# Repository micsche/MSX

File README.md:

# MSX
Recreate a Z80 system using MSX2 standard. 

The system is subdivided into 5 boards connected by a BUS. 

1. msx1-cpu: This is the CPU board complete with CPU, Clock circuit, Reset Circuit, IO Address decoder and default MSX Wait circuit.
2. msx1-memory : This is the 64k ROM/ 64k RAM circuit and a USB Serial connection via CJMCU-232H. Currently this is an MSX1 standard. 
3. msx1-keyb-ppi : This is the Keyboard connector circuit and the Memory Slot selector circuit
4. msx1-psg: This is the sound circuit (using YM2149). Joystick interface not implemented.
5. msx1-vdp: This is the video circuit (using TMS9958). To be completed: VRAM  of 96k possible.

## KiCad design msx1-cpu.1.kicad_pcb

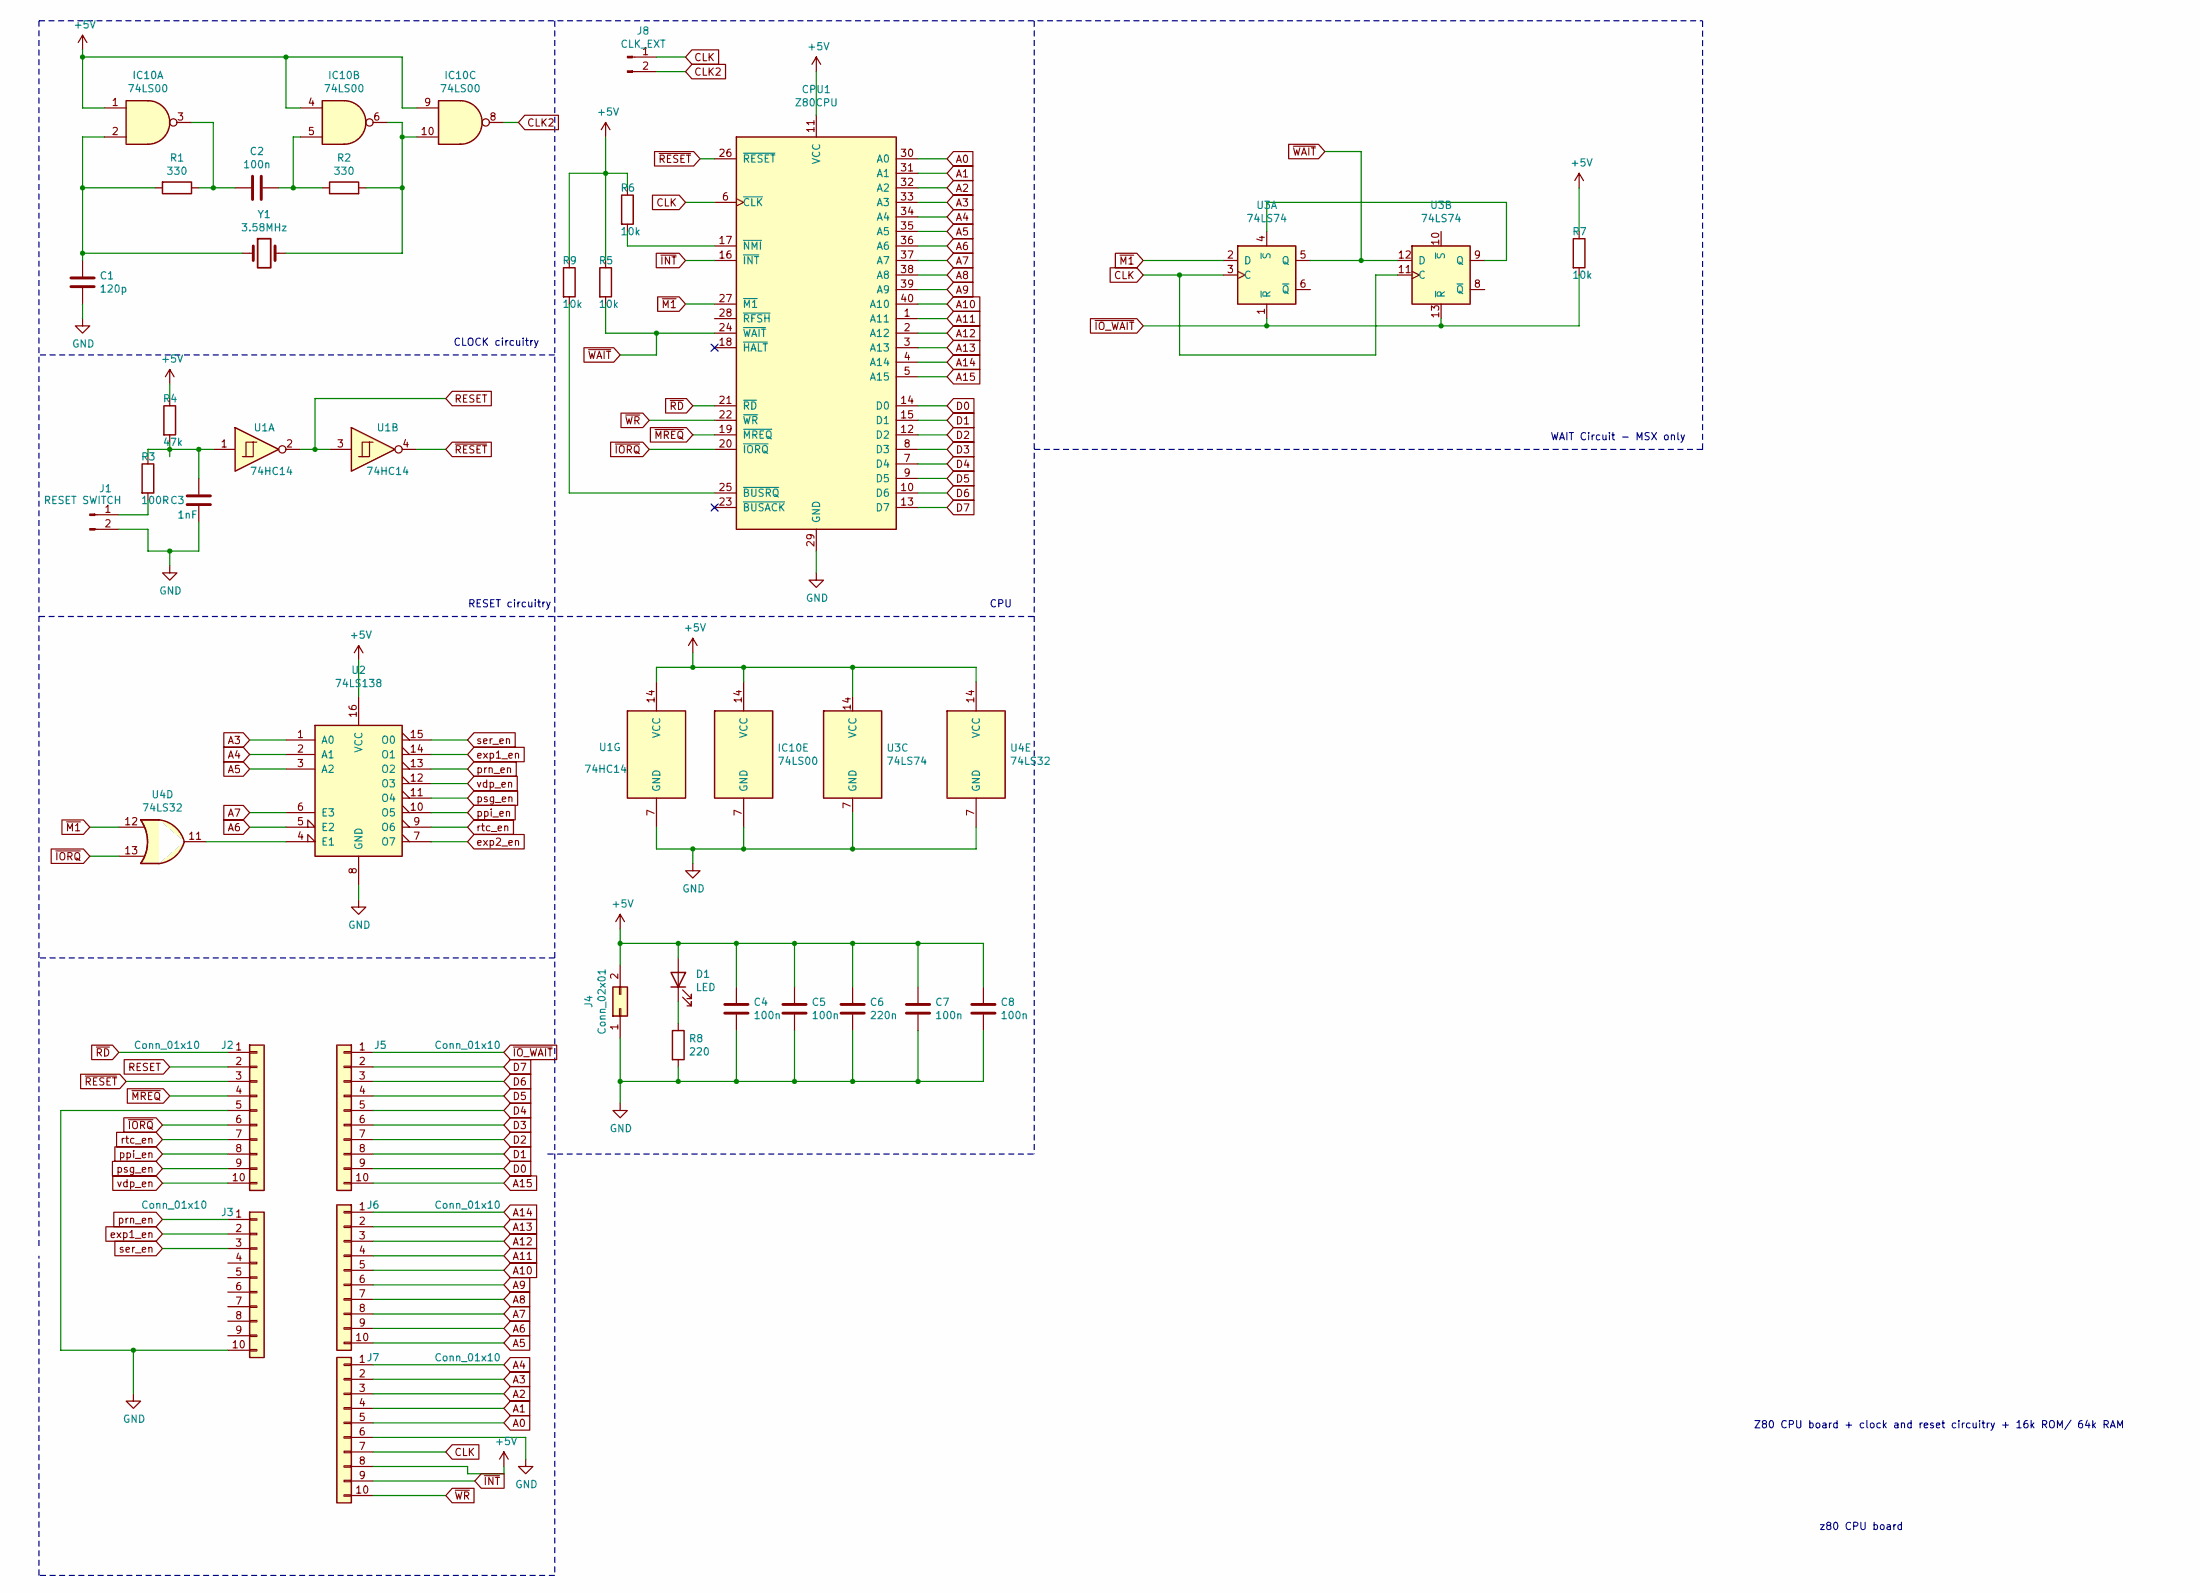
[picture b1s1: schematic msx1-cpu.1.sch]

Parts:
C1: 120p; CP_Radial_D4.0mm_P1.50mm
C2, C4, C5, C7, C8: 100n; C_Radial_D8.0mm_H7.0mm_P3.50mm
C3: 1nF; CP_Radial_D7.5mm_P2.50mm
C6: 220n; C_Radial_D8.0mm_H7.0mm_P3.50mm
CPU1: Z80CPU; DIP-40_W15.24mm_Socket
D1: LED; LED_D3.0mm_FlatTop
IC10: 74LS00; DIP-14_W7.62mm_LongPads
J1: RESET SWITCH; PinHeader_2x01_P2.54mm_Vertical
J2, J3, J5, J6, J7: Conn_01x10; PinHeader_1x10_P2.54mm_Vertical
J4: Conn_02x01; PinHeader_1x02_P2.54mm_Horizontal
J8: CLK_EXT; PinHeader_1x02_P2.54mm_Vertical
R1, R2: 330; R_Axial_DIN0207_L6.3mm_D2.5mm_P10.16mm_Horizontal
R3: 100R; R_Axial_DIN0207_L6.3mm_D2.5mm_P10.16mm_Horizontal
R4: 47k; R_Axial_DIN0207_L6.3mm_D2.5mm_P10.16mm_Horizontal
R5, R6, R7, R9: 10k; R_Axial_DIN0207_L6.3mm_D2.5mm_P10.16mm_Horizontal
R8: 220; R_Axial_DIN0207_L6.3mm_D2.5mm_P10.16mm_Horizontal
U1: 74HC14; DIP-14_W7.62mm_LongPads
U2: 74LS138; DIP-16_W7.62mm_Socket_LongPads
U3: 74LS74; DIP-14_W7.62mm_LongPads
U4: 74LS32; DIP-14_W7.62mm_LongPads
Y1: 3.58MHz; Crystal_HC49-U_Vertical

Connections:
+5V: C4.1, C5.1, C6.1, C7.1, C8.1, CPU1.11 (VCC), D1.2 (A), IC10.1, IC10.4, IC10.9, IC10.14 (VCC), J4.2, J7.8, R4.1, R5.1, R6.1, R7.1, R9.1, U1.14 (VCC), U2.16 (VCC), U3.14 (VCC), U4.14 (VCC); also elsewhere on the board
A0: CPU1.30 (A0), J7.5
A1: CPU1.31 (A1), J7.4
A2: CPU1.32 (A2), J7.3
A3: CPU1.33 (A3), J7.2, U2.1 (A0)
A4: CPU1.34 (A4), J7.1, U2.2 (A1)
A5: CPU1.35 (A5), J6.10, U2.3 (A2)
A6: CPU1.36 (A6), J6.9, U2.5 (E2)
A7: CPU1.37 (A7), J6.8, U2.6 (E3)
A8: CPU1.38 (A8), J6.7
A9: CPU1.39 (A9), J6.6
A10: CPU1.40 (A10), J6.5
A11: CPU1.1 (A11), J6.4
A12: CPU1.2 (A12), J6.3
A13: CPU1.3 (A13), J6.2
A14: CPU1.4 (A14), J6.1
A15: CPU1.5 (A15), J5.10
CLK: CPU1.6 (~CLK~), J7.7, J8.1, U3.3 (C), U3.11 (C)
CLK2: IC10.8, J8.2
D0: CPU1.14 (D0), J5.9
D1: CPU1.15 (D1), J5.8
D2: CPU1.12 (D2), J5.7
D3: CPU1.8 (D3), J5.6
D4: CPU1.7 (D4), J5.5
D5: CPU1.9 (D5), J5.4
D6: CPU1.10 (D6), J5.3
D7: CPU1.13 (D7), J5.2
GND: C1.2, C3.2, C4.2, C5.2, C6.2, C7.2, C8.2, CPU1.29 (GND), IC10.7 (GND), J1.2, J2.5, J3.10, J4.1, J7.6, R8.2, U1.7 (GND), U2.8 (GND), U3.7 (GND), U4.7 (GND); also elsewhere on the board
unnamed: C1.1, IC10.2, R1.2, Y1.1
unnamed: C2.1, IC10.5, R2.1
unnamed: C2.2, IC10.3, R1.1
unnamed: C3.1, R3.1, R4.2, U1.1
unnamed: CPU1.17 (~NMI~), R6.2
unnamed: CPU1.25 (~BUSRQ~), R9.2
unnamed: D1.1 (K), R8.1
unnamed: IC10.6, IC10.10, R2.2, Y1.2
unnamed: J1.1, R3.2
unnamed: U2.4 (E1), U4.11
unnamed: U3.4 (~S), U3.9 (Q)
RESET: J2.2, U1.2, U1.3
exp1_en: J3.2, U2.14 (O1)
exp2_en: U2.7 (O7)
ppi_en: J2.8, U2.10 (O5)
prn_en: J3.1, U2.13 (O2)
psg_en: J2.9, U2.11 (O4)
rtc_en: J2.7, U2.9 (O6)
ser_en: J3.3, U2.15 (O0)
vdp_en: J2.10, U2.12 (O3)
~INT: CPU1.16 (~INT~), J7.9
~IORQ: CPU1.20 (~IORQ~), J2.6, U4.13
~IO_WAIT: J5.1, R7.2, U3.1 (~R), U3.13 (~R)
~M1: CPU1.27 (~M1~), U3.2 (D), U4.12
~MREQ: CPU1.19 (~MREQ~), J2.4
~RD: CPU1.21 (~RD~), J2.1
~RESET: CPU1.26 (~RESET~), J2.3, U1.4
~WAIT: CPU1.24 (~WAIT~), R5.2, U3.5 (Q), U3.12 (D)
~WR: CPU1.22 (~WR~), J7.10

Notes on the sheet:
Z80 CPU board + clock and reset circuitry + 16k ROM/ 64k RAM
z80 CPU board
CLOCK circuitry
RESET circuitry
CPU
WAIT Circuit - MSX only

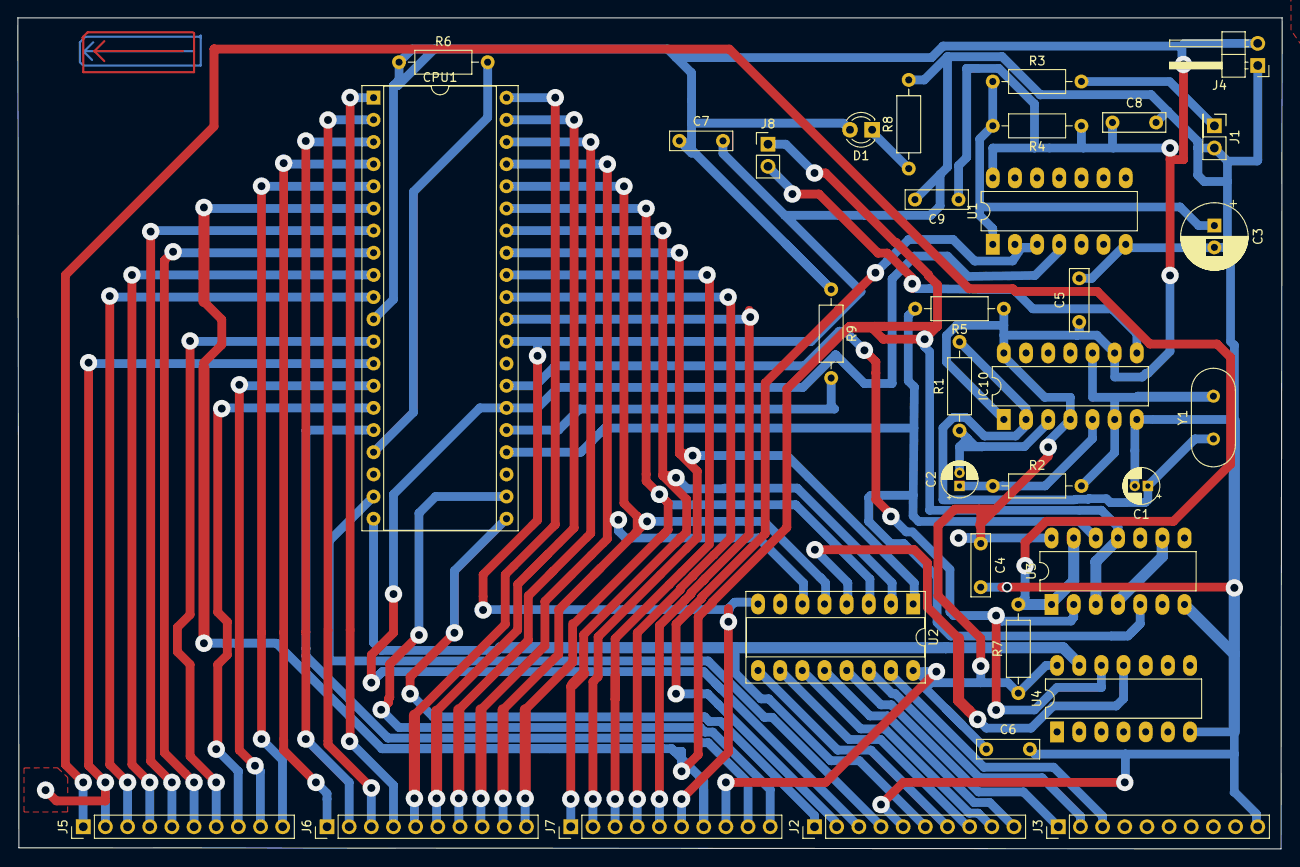
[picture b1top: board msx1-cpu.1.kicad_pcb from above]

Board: 2 copper layers, 144.9 x 95.2 mm, 34 parts (0 on the bottom side), 56 nets.

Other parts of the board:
C9: 100n; C_Rect_L7.0mm_W2.0mm_P5.00mm

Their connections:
+5V: C9.1; also elsewhere on the board
GND: C9.2; also elsewhere on the board

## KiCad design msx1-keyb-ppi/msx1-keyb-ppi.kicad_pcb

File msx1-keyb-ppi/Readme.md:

# MSX PPI - Keyboard Interface (as of writing untested)

This board has two functions:
1. Interface with a matrix keyboard (in progress), including an LED output for the CAPS lock key.
2. Provide SLOT Signalling standard of MSX

## Keyboard

The board has a DB25 connector where a keyboard is to be connected.

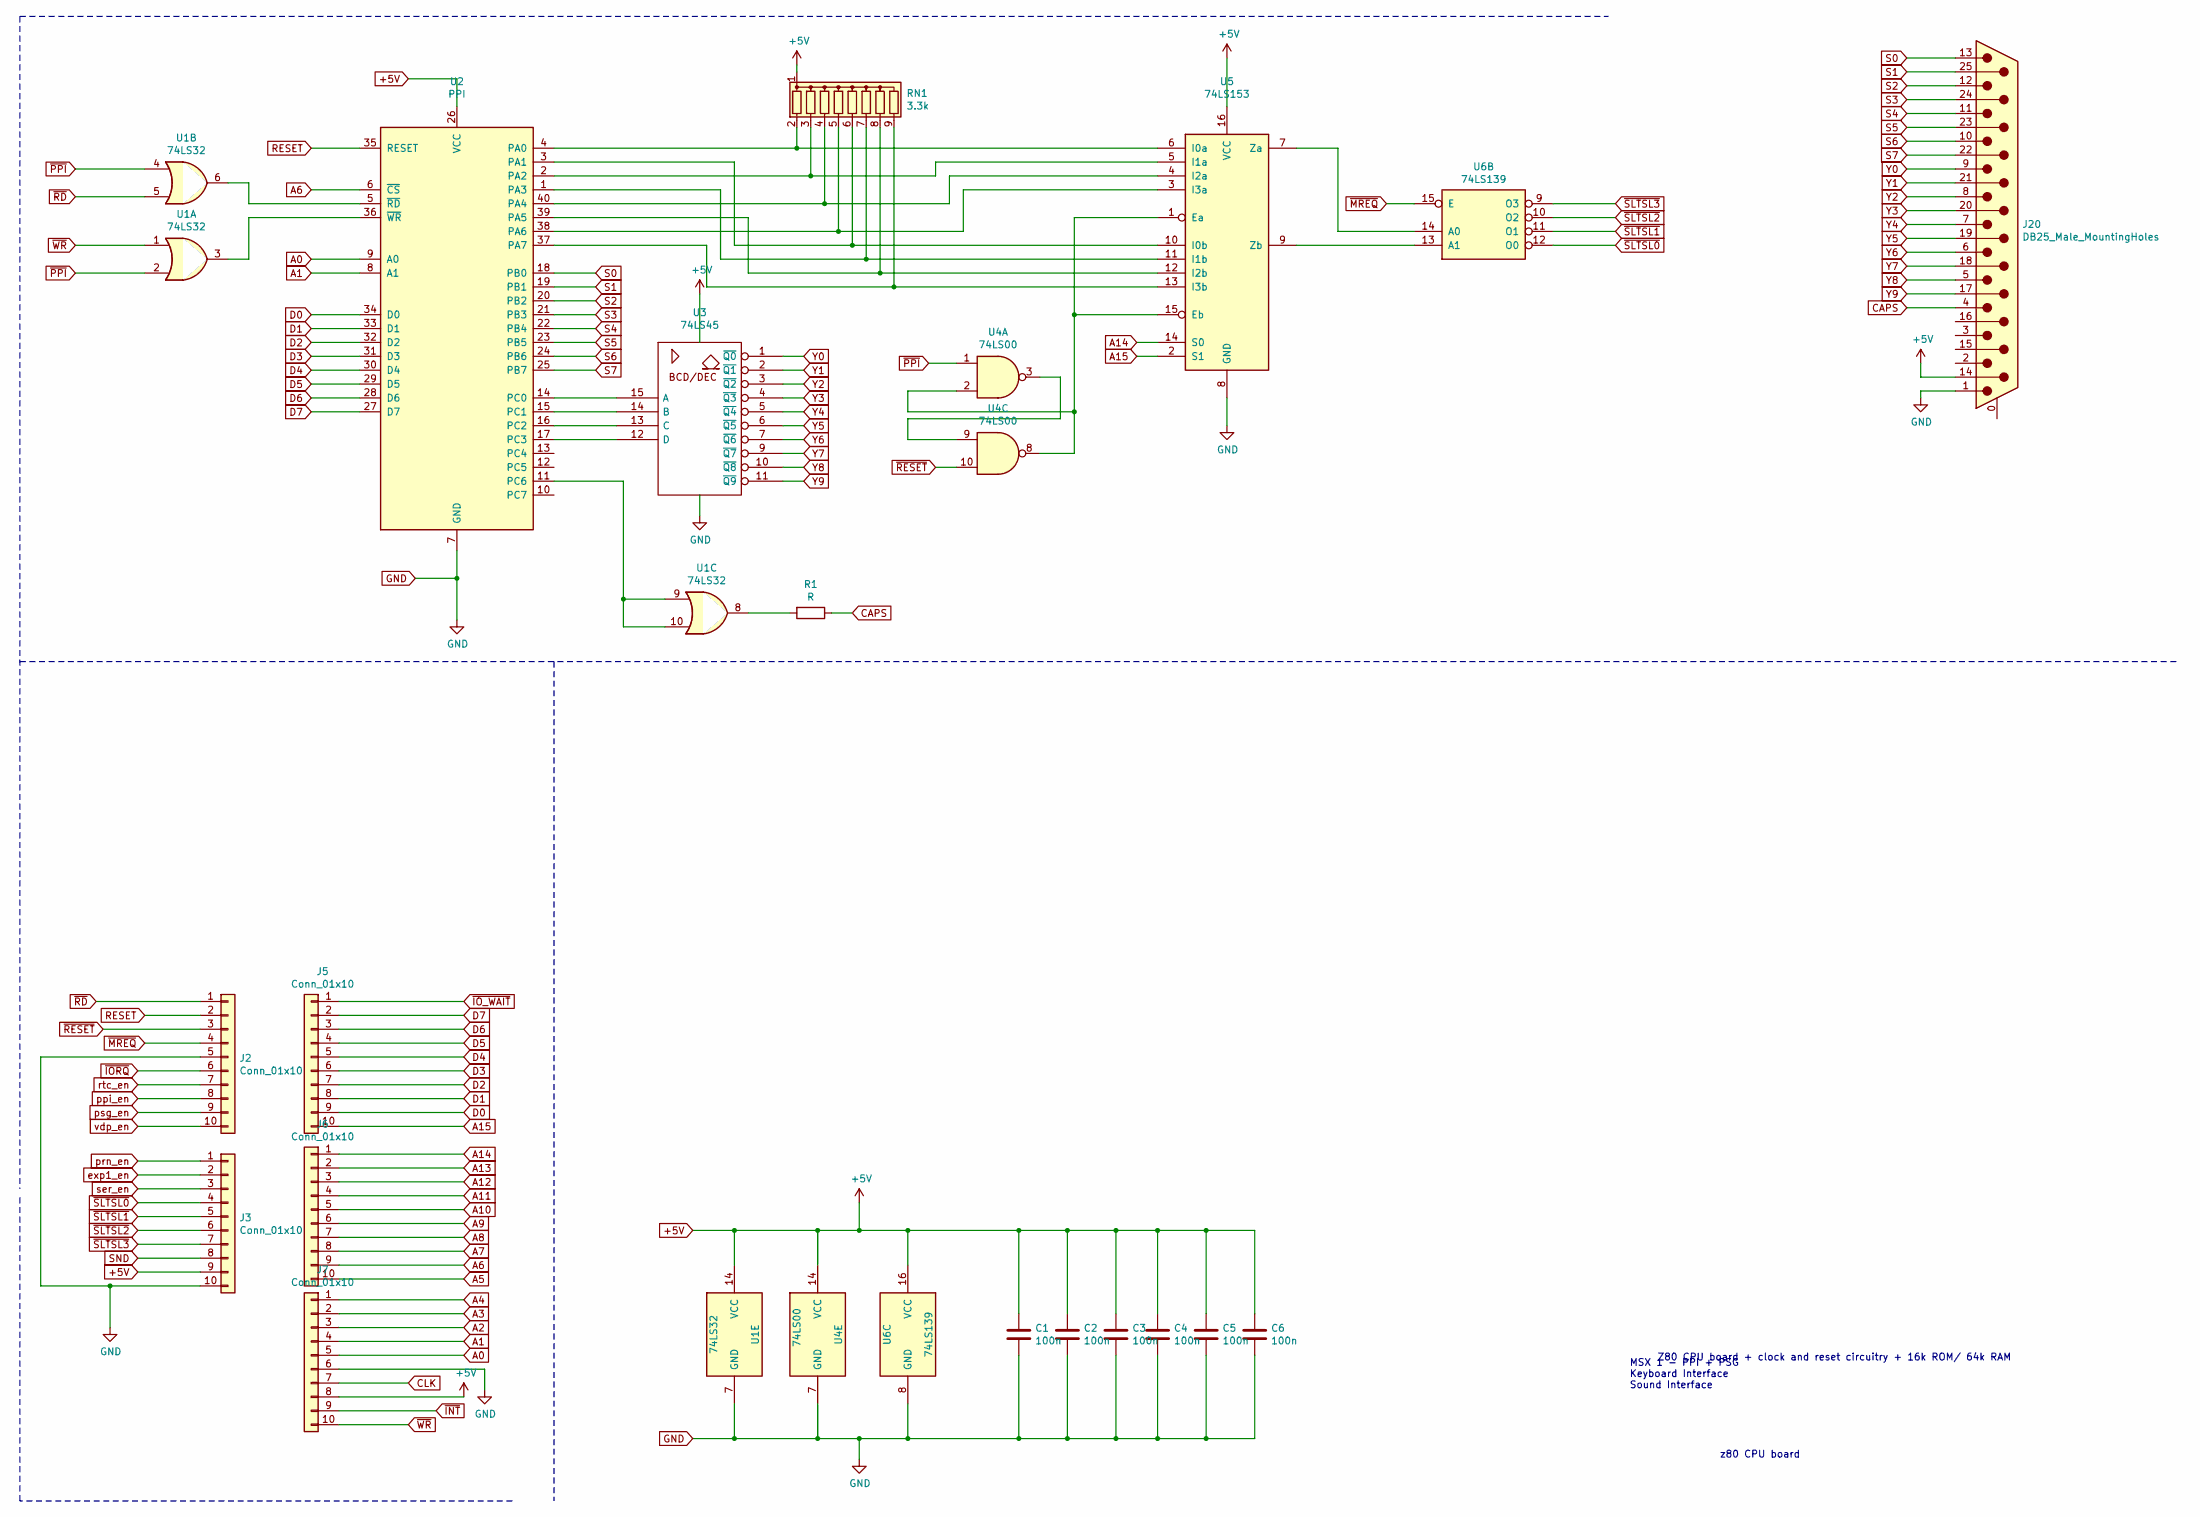
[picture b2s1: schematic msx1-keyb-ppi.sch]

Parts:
C1, C2, C3, C4, C5, C6: 100n; C_Rect_L7.0mm_W2.0mm_P5.00mm
J2, J3, J5, J6, J7: Conn_01x10; PinHeader_1x10_P2.54mm_Vertical
J20: DB25_Male_MountingHoles; DSUB-25_Male_Horizontal_P2.77x2.84mm_EdgePinOffset7.70mm_Ho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
R1: R; R_Axial_DIN0207_L6.3mm_D2.5mm_P7.62mm_Horizontal
RN1: 3.3k; R_Array_SIP9
U1: 74LS32; DIP-14_W7.62mm_LongPads
U2: PPI; DIP-40_W15.24mm_LongPads
U3: 74LS45; DIP-16_W10.16mm_LongPads
U4: 74LS00; DIP-14_W7.62mm_LongPads
U5: 74LS153; DIP-16_W10.16mm_LongPads
U6: 74LS139; DIP-16_W10.16mm_LongPads

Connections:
+5V: C1.1, C2.1, C3.1, C4.1, C5.1, C6.1, J3.9, J7.8, J20.14, RN1.1 (common), U1.14 (VCC), U2.26 (VCC), U3.16 (VCC), U4.14 (VCC), U5.16 (VCC), U6.16 (VCC)
A0: J7.5, U2.9 (A0)
A1: J7.4, U2.8 (A1)
A2: J7.3
A3: J7.2
A4: J7.1
A5: J6.10
A6: J6.9, U2.6 (~CS~)
A7: J6.8
A8: J6.7
A9: J6.6
A10: J6.5
A11: J6.4
A12: J6.3
A13: J6.2
A14: J6.1, U5.14 (S0)
A15: J5.10, U5.2 (S1)
CAPS: J20.4, R1.1
CLK: J7.7
D0: J5.9, U2.34 (D0)
D1: J5.8, U2.33 (D1)
D2: J5.7, U2.32 (D2)
D3: J5.6, U2.31 (D3)
D4: J5.5, U2.30 (D4)
D5: J5.4, U2.29 (D5)
D6: J5.3, U2.28 (D6)
D7: J5.2, U2.27 (D7)
GND: C1.2, C2.2, C3.2, C4.2, C5.2, C6.2, J2.5, J3.10, J7.6, J20.1, U1.7 (GND), U2.7 (GND), U3.8 (GND), U4.7 (GND), U5.8 (GND), U6.8 (GND)
unnamed: R1.2, U1.8
unnamed: RN1.2 (R1), U2.4 (PA0), U5.6 (I0a)
unnamed: RN1.3 (R2), U2.2 (PA2), U5.5 (I1a)
unnamed: RN1.4 (R3), U2.40 (PA4), U5.4 (I2a)
unnamed: RN1.5 (R4), U2.38 (PA6), U5.3 (I3a)
unnamed: RN1.6 (R5), U2.3 (PA1), U5.10 (I0b)
unnamed: RN1.7 (R6), U2.1 (PA3), U5.11 (I1b)
unnamed: RN1.8 (R7), U2.39 (PA5), U5.12 (I2b)
unnamed: RN1.9 (R8), U2.37 (PA7), U5.13 (I3b)
unnamed: U1.3, U2.36 (~WR~)
unnamed: U1.6, U2.5 (~RD~)
unnamed: U1.9, U1.10, U2.11 (PC6)
unnamed: U2.14 (PC0), U3.15 (A)
unnamed: U2.15 (PC1), U3.14 (B)
unnamed: U2.16 (PC2), U3.13 (C)
unnamed: U2.17 (PC3), U3.12 (D)
unnamed: U4.2, U4.8, U5.1 (Ea), U5.15 (Eb)
unnamed: U4.3, U4.9
unnamed: U5.7 (Za), U6.14 (A0)
unnamed: U5.9 (Zb), U6.13 (A1)
RESET: J2.2, U2.35 (RESET)
S0: J20.13, U2.18 (PB0)
S1: J20.25, U2.19 (PB1)
S2: J20.12, U2.20 (PB2)
S3: J20.24, U2.21 (PB3)
S4: J20.11, U2.22 (PB4)
S5: J20.23, U2.23 (PB5)
S6: J20.10, U2.24 (PB6)
S7: J20.22, U2.25 (PB7)
SND: J3.8
Y0: J20.9, U3.1 (~Q0)
Y1: J20.21, U3.2 (~Q1)
Y2: J20.8, U3.3 (~Q2)
Y3: J20.20, U3.4 (~Q3)
Y4: J20.7, U3.5 (~Q4)
Y5: J20.19, U3.6 (~Q5)
Y6: J20.6, U3.7 (~Q6)
Y7: J20.18, U3.9 (~Q7)
Y8: J20.5, U3.10 (~Q8)
Y9: J20.17, U3.11 (~Q9)
exp1_en: J3.2
ppi_en: J2.8
prn_en: J3.1
psg_en: J2.9
rtc_en: J2.7
ser_en: J3.3
vdp_en: J2.10
~INT: J7.9
~IORQ: J2.6
~IO_WAIT: J5.1
~MREQ: J2.4, U6.15 (E)
~PPI: U1.2, U1.4, U4.1
~RD: J2.1, U1.5
~RESET: J2.3, U4.10
~SLTSL0: J3.4, U6.12 (O0)
~SLTSL1: J3.5, U6.11 (O1)
~SLTSL2: J3.6, U6.10 (O2)
~SLTSL3: J3.7, U6.9 (O3)
~WR: J7.10, U1.1

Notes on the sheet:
MSX 1 - PPI + PSG Keyboard Interface Sound Interface
Z80 CPU board + clock and reset circuitry + 16k ROM/ 64k RAM
z80 CPU board

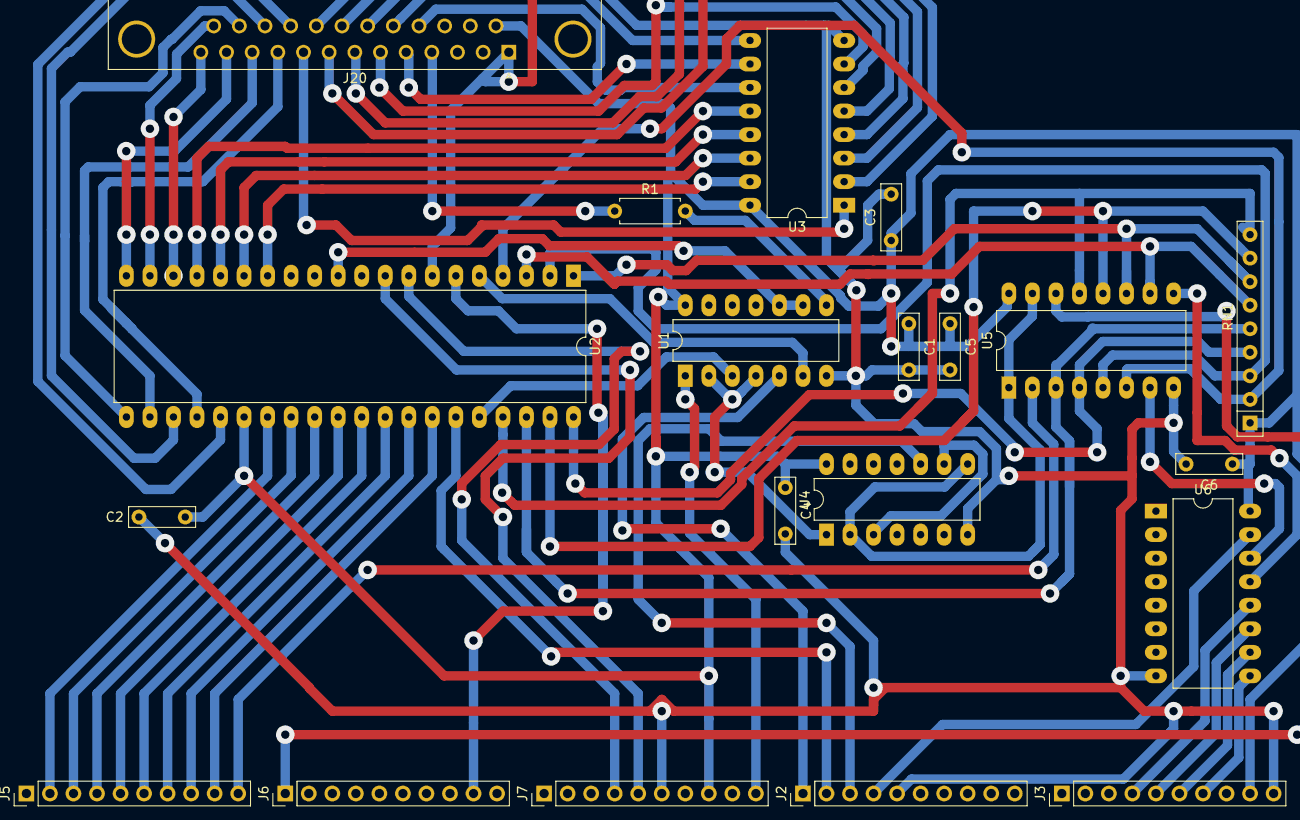
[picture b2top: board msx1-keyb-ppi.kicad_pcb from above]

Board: 2 copper layers, 20 parts (0 on the bottom side), 64 nets.

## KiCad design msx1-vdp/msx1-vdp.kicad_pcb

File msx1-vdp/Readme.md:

# MSX Video

This is a work in progress.

The VDP9958 is used (although this is not used until the MSX2+ standard)

The chip requires the use of DRAM chips. The use of SRAM would require complex address decode, out of the scope of this board development.
A 128k VRAM is possible with V9958.

The Video chips use the Z80 interrupt signal and also provide a CPU clock signal.

The video signal needs to be modified for use of new displays. LED displays cannot handle the 15kHz HSYNC frequency used by the chip.

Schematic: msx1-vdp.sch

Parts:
C1: 15pf; C_Disc_D5.0mm_W2.5mm_P2.50mm
C2: 7pF; C_Disc_D5.0mm_W2.5mm_P2.50mm
C3, C4, C5, C6, C7, C8: C; C_Rect_L7.0mm_W2.0mm_P5.00mm
J1: Conn_02x03_Counter_Clockwise; IDC-Header_2x04_P2.54mm_Vertical
J2, J3, J5, J6, J7: Conn_01x10; PinHeader_1x10_P2.54mm_Vertical
JP1: Jumper_NO_Small; Molex_KK-254_AE-6410-02A_1x02_P2.54mm_Vertical
R1: 330; R_Axial_DIN0207_L6.3mm_D2.5mm_P5.08mm_Vertical
U1: 74LS32; DIP-14_W7.62mm_Socket
U2: TMS9958-MSX; DIP-64_W25.4mm_LongPads
U4: 74LS00; DIP-14_W7.62mm_LongPads
U5: 74LS74; DIP-14_W7.62mm_LongPads
U6, U7: 74LS574; DIP-20_W7.62mm_LongPads
U8: 551001; DIP-32_W15.24mm_LongPads
Y1: 21.47727MHz; Resonator-2Pin_W6.0mm_H3.0mm

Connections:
+5V: C3.1, C4.1, C5.1, C6.1, C7.1, C8.1, J1.1, J3.9, J7.8, U1.14 (VCC), U2.21, U2.58, U4.14 (VCC), U5.4 (~S), U5.14 (VCC), U6.20, U7.20, U8.8
A0: J7.5, U2.29
A1: J7.4, U2.28
A2: J7.3
A3: J7.2
A4: J7.1
A5: J6.10
A6: J6.9
A7: J6.8
A8: J6.7
A9: J6.6
A10: J6.5
A11: J6.4
A12: J6.3
A13: J6.2
A14: J6.1
A15: J5.10
ADD_DATA_0: U2.49, U6.2, U7.2
ADD_DATA_1: U2.50, U6.3, U7.3
ADD_DATA_2: U2.51, U6.4, U7.4
ADD_DATA_3: U2.52, U6.5, U7.5
ADD_DATA_4: U2.53, U6.6, U7.6
ADD_DATA_5: U2.54, U6.7, U7.7
ADD_DATA_6: U2.55, U6.8, U7.8
ADD_DATA_7: U2.56, U6.9, U7.9
B: J1.6, U2.24
CAS: U4.3, U4.12, U4.13, U5.3 (C), U7.11
CLK: J7.7, JP1.1
CSYNC: J1.2, U2.6
D0: J5.9, U2.40
D1: J5.8, U2.39
D2: J5.7, U2.38
D3: J5.6, U2.37
D4: J5.5, U2.36
D5: J5.4, U2.35
D6: J5.3, U2.34
D7: J5.2, U2.32
DATA0: U2.41, U8.21
DATA1: U2.42, U8.22
DATA2: U2.43, U8.23
DATA3: U2.44, U8.25
DATA4: U2.45, U8.26
DATA5: U2.46, U8.27
DATA6: U2.47, U8.28
DATA7: U2.48, U8.29
G: J1.7, U2.22
GND: C1.1, C2.1, C3.2, C4.2, C5.2, C6.2, C7.2, C8.2, J1.4, J2.5, J3.10, J7.6, U1.7 (GND), U2.1, U2.20, U4.7 (GND), U5.1 (~R), U5.7 (GND), U6.1, U6.10, U7.1, U7.10, U8.24
unnamed: C1.2, R1.1, Y1.1
unnamed: C2.2, U2.63, Y1.2
unnamed: JP1.2, U2.8
unnamed: R1.2, U2.64
unnamed: U1.3, U2.31
unnamed: U1.6, U2.30
unnamed: U2.60, U4.2, U5.2 (D)
unnamed: U2.61, U4.1
unnamed: U4.6, U6.11
unnamed: U4.8, U8.32
unnamed: U4.11, U8.6, U8.30
unnamed: U5.5 (Q), U8.10
unnamed: U6.12, U8.13
unnamed: U6.13, U8.14
unnamed: U6.14, U8.15
unnamed: U6.15, U8.16
unnamed: U6.16, U8.17
unnamed: U6.17, U8.18
unnamed: U6.18, U8.19
unnamed: U6.19, U8.20
unnamed: U7.12, U8.7
unnamed: U7.13, U8.11
unnamed: U7.14, U8.4
unnamed: U7.15, U8.12
unnamed: U7.16, U8.1
unnamed: U7.17, U8.31
unnamed: U7.18, U8.2
unnamed: U7.19, U8.3
R: J1.8, U2.23
RESET: J2.2
R_~W: U2.57, U4.9, U4.10, U8.5
SND: J3.8
exp1_en: J3.2
ppi_en: J2.8
prn_en: J3.1
psg_en: J2.9
rtc_en: J2.7
ser_en: J3.3
vdp_en: J2.10, U1.2, U1.4
~HSYNC: J1.5, U2.5
~INT: J7.9, U2.25
~IORQ: J2.6
~IOWAIT: U2.26
~IO_WAIT: J5.1
~MREQ: J2.4
~RAS: U2.62, U4.4, U4.5
~RD: J2.1, U1.1
~RESET: J2.3, U2.9
~SLTSL0: J3.4
~SLTSL1: J3.5
~SLTSL2: J3.6
~SLTSL3: J3.7
~WR: J7.10, U1.5

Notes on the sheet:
Z80 CPU board + clock and reset circuitry + 16k ROM/ 64k RAM
z80 CPU board

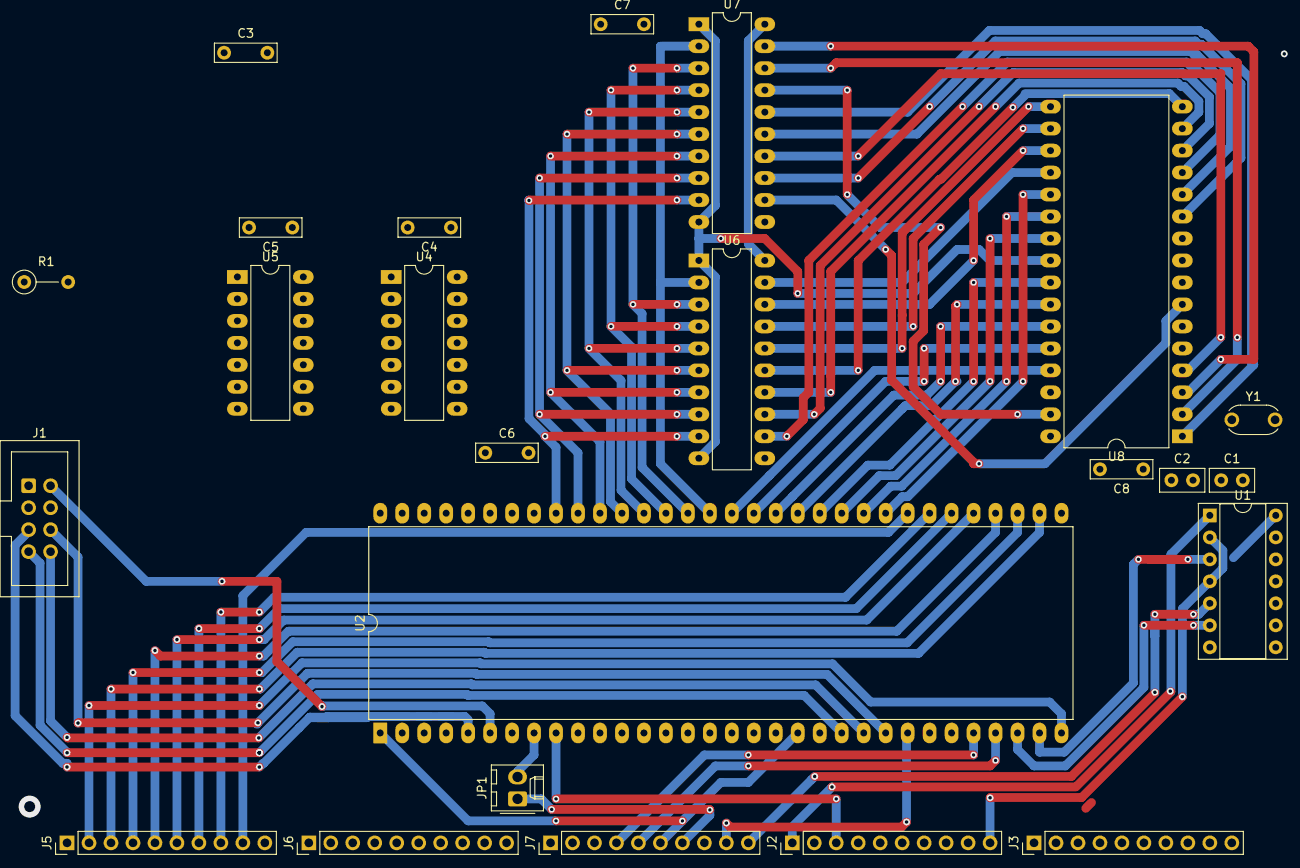
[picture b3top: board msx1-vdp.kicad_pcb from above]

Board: 2 copper layers, 24 parts (0 on the bottom side), 70 nets.

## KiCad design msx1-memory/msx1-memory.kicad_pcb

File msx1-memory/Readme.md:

# MSX Memory Board

The aim of the board is to use stock ROM and SRAM,  had available. Although the ROM and RAM used are 128k, only 64k are used. An MSX memory mapper is a future project.
For MSX to use the memory the PPI board is a required board since it decodes the Memory Slot SLTSL signal. In this case SLOT0 is used for ROM and SLOT3 is used for RAM. However, for the SBC there is included a simple decoder that can be switched off.

The MSX1 standard: ROM is using the first 32k address 0000-7FFF (normally at SLOT0), and 8k-32k RAM the subsequent 8000-FFFF (Normally at SLOT3).
- https://www.msx.org/wiki/The_Memory
- https://konamiman.github.io/MSX2-Technical-Handbook/md/Chapter1.html#1-from-msx1-to-msx2

## Using the board for SBC operation
This board is adapted to be used as an SBC. A modification on the ROM should remove the A15 address decoding to use just 32k.
This is done using a 74LS139 that decodes the A15 and MREQ to produce the SLTSL0 and SLTSL3 selector signals. 
When used in MSX mode the 74LS139 can be disabled by disconnecting jumper SimpleMem (which powers the Logic Circuit).

## Serial Connection
The board also uses the IO Serial signal to connect a USB Serial connection to the Z80 databus. The circuit interfaces with a breakout board CJMCU-232H, which is TTL compliant.

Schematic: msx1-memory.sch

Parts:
C1, C2, C3: 100n; C_Rect_L7.0mm_W2.0mm_P5.00mm
J1: SimpleMem; PinHeader_1x02_P2.54mm_Vertical
J2, J3, J5, J6, J7: Conn_01x10; PinHeader_1x10_P2.54mm_Vertical
J4: SimpleMem-INT; PinHeader_1x02_P2.54mm_Vertical
R1: 10k; R_Axial_DIN0207_L6.3mm_D2.5mm_P7.62mm_Horizontal
R2: 10k; R_Axial_DIN0207_L6.3mm_D2.5mm_P10.16mm_Horizontal
U1: ROM 29F010; DIP-32_W15.24mm_LongPads
U2: 74LS139; DIP-16_W7.62mm_LongPads
U3: SRAM TC551001; DIP-32_W15.24mm_LongPads
U5: CJMCU-232H; CJMCU-232H-Breakout

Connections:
3.3V: U5.13
+5V: C1.1, C2.1, C3.1, J1.1, J3.9, J4.1, J7.8, R2.1, U1.32, U3.32, U5.9, U5.14
A0: J7.5, U1.12, U3.12, U5.16
A1: J7.4, U1.11, U3.11
A2: J7.3, U1.10, U3.10
A3: J7.2, U1.9, U3.9
A4: J7.1, U1.8, U3.8
A5: J6.10, U1.7, U3.7
A6: J6.9, U1.6, U3.6
A7: J6.8, U1.5, U3.5
A8: J6.7, U1.27, U3.27
A9: J6.6, U1.26, U3.26
A10: J6.5, U1.23, U3.23
A11: J6.4, U1.25, U3.25
A12: J6.3, U1.4, U3.4
A13: J6.2, U1.28, U3.28
A14: J6.1, U1.29, U3.3
A15: J5.10, U1.3, U2.2, U3.31
CLK: J7.7
D0: J5.9, U1.13, U3.13, U5.1
D1: J5.8, U1.14, U3.14, U5.2
D2: J5.7, U1.15, U3.15, U5.3
D3: J5.6, U1.17, U3.17, U5.4
D4: J5.5, U1.18, U3.18, U5.5
D5: J5.4, U1.19, U3.19, U5.6
D6: J5.3, U1.20, U3.20, U5.7
D7: J5.2, U1.21, U3.21, U5.8
GND: C1.2, C2.2, C3.2, J2.5, J3.10, J7.6, U1.2, U1.16, U2.3, U2.8, U3.2, U3.16, U5.10, U5.11
unnamed: J1.2, U2.16
unnamed: J4.2, R1.1
unnamed: R2.2, U3.30
RESET: J2.2
SND: J3.8
exp1_en: J3.2
ppi_en: J2.8
prn_en: J3.1
psg_en: J2.9
rtc_en: J2.7
ser_en: J3.3, U5.15
vdp_en: J2.10
~INT: J7.9, R1.2
~IORQ: J2.6
~IO_WAIT: J5.1
~MREQ: J2.4, U2.1
~RD: J2.1, U1.24, U3.24, U5.17
~RESET: J2.3
~SLTSL0: J3.4, U1.22, U2.4
~SLTSL1: J3.5
~SLTSL2: J3.6
~SLTSL3: J3.7, U2.5, U3.22
~WR: J7.10, U3.29, U5.18

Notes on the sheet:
z80 CPU board
Z80 64k ROM/ 64k RAM
TC551001 - 128k 8bit -70 70ns -100 100ns
29F010 - 128k 45-120ns
ROM -CE <= -SLTSL0 dependant on -MREQ or -RFSH RAM -CS <= SLTSL3 dependant on -MREQ or -RFSH
Z80 USB serial
SimpleMem jumper Jumper on - RAM/ROM Jumper off - SLTSL3/SLTSL0 from MSX circuitry
SimpleMem jumper INT -> 5V

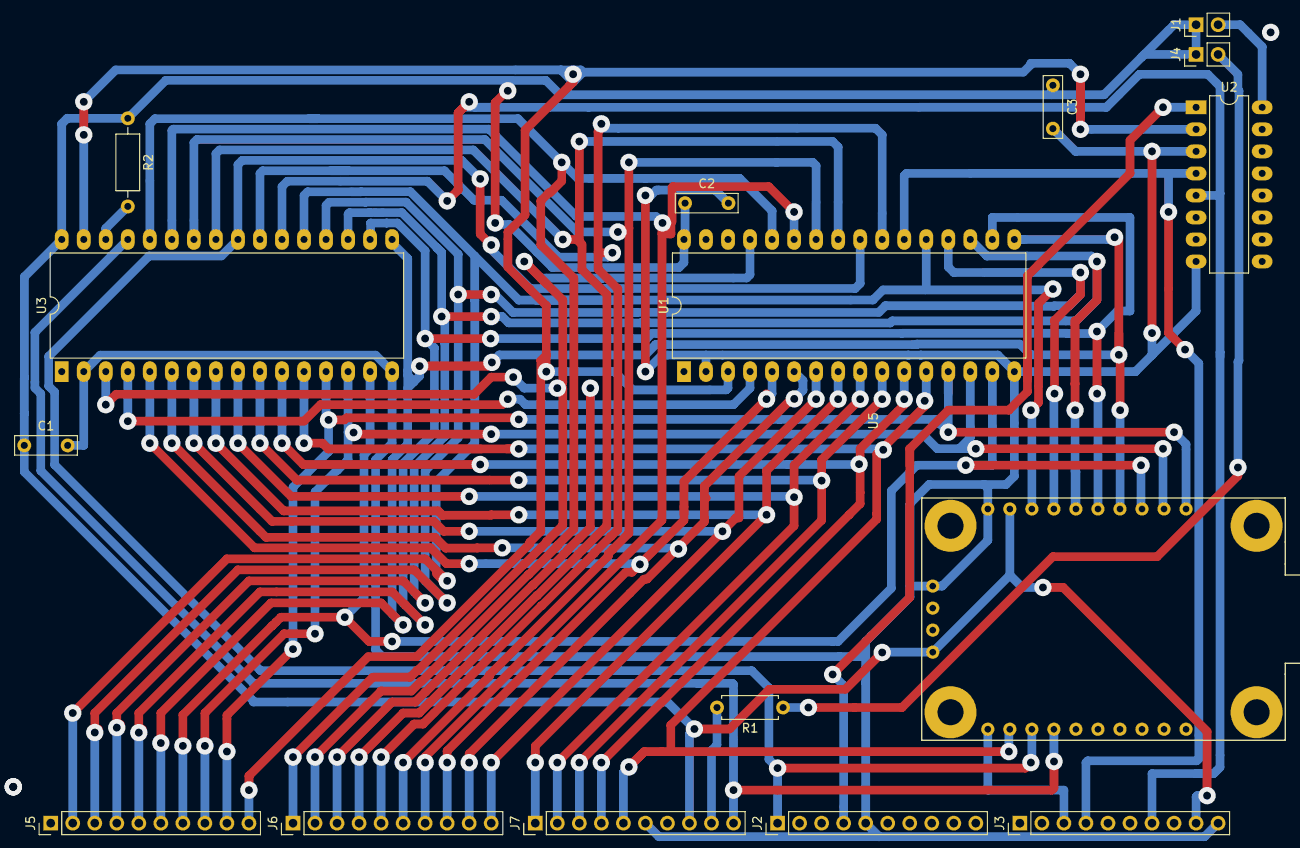
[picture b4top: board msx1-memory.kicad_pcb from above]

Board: 2 copper layers, 16 parts (0 on the bottom side), 36 nets.
